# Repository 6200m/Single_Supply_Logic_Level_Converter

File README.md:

SparkFun Single Supply Logic Level Converter
========================================

[*SparkFun Single Supply Logic Level Converter (PRT-14765)*](https://www.sparkfun.com/products/14765)

The SparkFun Single Supply Logic Level Converter is logic level and power supply translator in one small package. This little board breaks out the Texas Instruments TXB0104 4-bit bi-directional voltage-level translator with automatic direction sensing. With this logic level converter you will be able to use your 5V logic microcontroller with 3.3V sensors without the second power supply!

What makes this logic level converter truly special is the fact that you can supply it with 3.3V and it will create the 5V - meaning you can use your 3.3V system, and convert directly to another 5V sensor - and even power your sensor or other board!

This logic level converter provides 5V to the high side of the TXB0104 and the low side is programmable to 3.3V, 2.5V and 1.8V. Please keep in mind that the default low side voltage is 3.3V.

Repository Contents
-------------------
* **/Firmware** - Example code 
* **/Hardware** - Eagle design files (.brd, .sch)
* **/Production** - Production panel files (.brd)

Documentation
--------------
* **[Hookup Guide](https://learn.sparkfun.com/tutorials/single-supply-logic-level-converter-hook-up-guide)** - Basic hookup guide for the Single Supply Logic Level Converter.
* **[SparkFun Fritzing repo](https://github.com/sparkfun/Fritzing_Parts)** - Fritzing diagrams for SparkFun products.

Product Versions
----------------
* [PRT-14765](https://www.sparkfun.com/products/14765)- V1.0

License Information
-------------------

This product is _**open source**_! 

Please review the LICENSE.md file for license information. 

If you have any questions or concerns on licensing, please contact techsupport@sparkfun.com.

Distributed as-is; no warranty is given.

- Your friends at SparkFun.

_<COLLABORATION CREDIT>_

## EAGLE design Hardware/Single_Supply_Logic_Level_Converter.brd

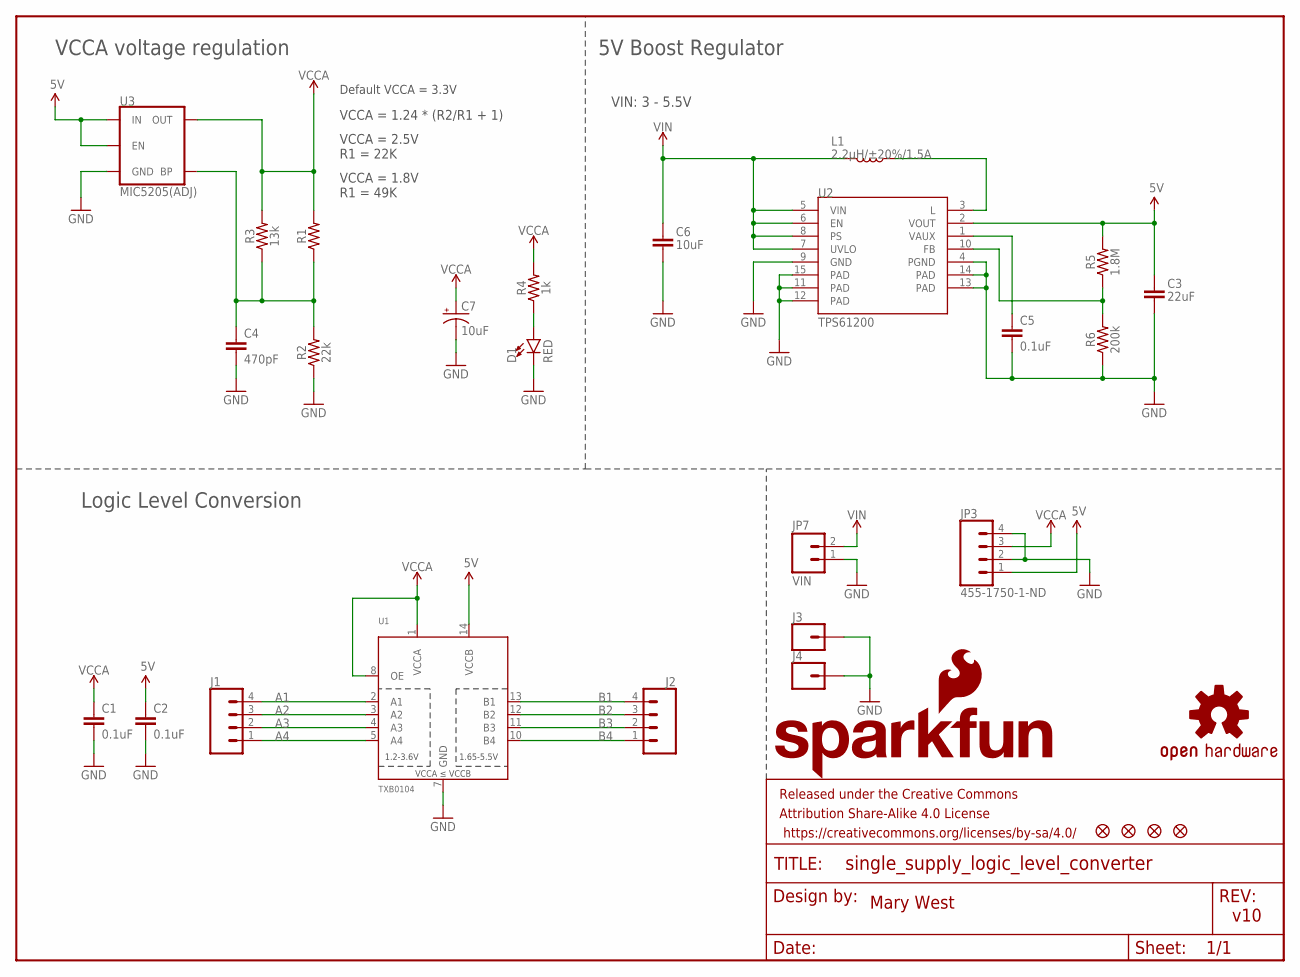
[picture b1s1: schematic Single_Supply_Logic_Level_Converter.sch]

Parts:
C1, C2: 0.1uF; 0603-CAP
C3: 22uF; 0805
C4: 470pF; 0603
C5: 0.1uF; 0603
C6: 10uF; 0603
C7: 10uF; EIA3216
D1: RED; LED-0603
FD1, FD2, FD3, FD4: FIDUCIALUFIDUCIAL; FIDUCIAL-MICRO
FRAME1: FRAME-LETTER; CREATIVE_COMMONS
J1, J2: CONN_04; 1X04
J3, J4: CONN_01; 1X01
JP3: 455-1750-1-ND; 1X04
JP7: VIN; 1X02
L1: 2.2µH/±20%/1.5A; INDUCTOR_2.2UH
LOGO1: SFE_LOGO_NAME_FLAME.1_INCH; SFE_LOGO_NAME_FLAME_.1
LOGO2: OSHW-LOGOS; OSHW-LOGO-S
R1: AXIAL-0.3
R2: 22k; 0603
R3: 13k; 0603
R4: 1k; 0603
R5: 1.8M; 0603
R6: 200k; 0603
U1: TXB0104; TSSOP14
U2: TPS61200; QFN-10_PAD
U3: MIC5205(ADJ); SOT23-5

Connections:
5V: C2.1, C3.1, JP3.1, R5.2, U1.14 (VCCB), U2.2 (VOUT), U3.1 (IN), U3.3 (EN)
A1: J1.4, U1.2 (A1)
A2: J1.3, U1.3 (A2)
A3: J1.2, U1.4 (A3)
A4: J1.1, U1.5 (A4)
B1: J2.4, U1.13 (B1)
B2: J2.3, U1.12 (B2)
B3: J2.2, U1.11 (B3)
B4: J2.1, U1.10 (B4)
FB: R5.1, R6.2, U2.10 (FB)
GND: C1.2, C2.2, C3.2, C4.2, C5.2, C6.2, C7.-, D1.C, J3.1, J4.1, JP3.2, JP3.4, JP7.1, R2.1, R6.1, U1.7 (GND), U2.4 (PGND), U2.9 (GND), U2.11 (PAD), U2.12 (PAD), U2.13 (PAD), U2.14 (PAD), U2.15 (PAD), U3.2 (GND)
unnamed: D1.A, R4.1
unnamed: L1.P$1 (1), U2.3 (L)
unnamed: C5.1, U2.1 (VAUX)
unnamed: C4.1, R1.P$1 (1), R2.2, R3.1, U3.4 (BP)
VCCA: C1.1, C7.+, JP3.3, R1.P$2 (2), R3.2, R4.2, U1.1 (VCCA), U1.8 (OE), U3.5 (OUT)
VIN: C6.1, JP7.2, L1.P$2 (2), U2.5 (VIN), U2.6 (EN), U2.7 (UVLO), U2.8 (PS)

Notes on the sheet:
Mary West
v10
VIN: 3 - 5.5V
Default VCCA = 3.3V
Logic Level Conversion
VCCA voltage regulation
5V Boost Regulator
VCCA = 1.24 * (R2/R1 + 1)
VCCA = 2.5V R1 = 22K
VCCA = 1.8V R1 = 49K

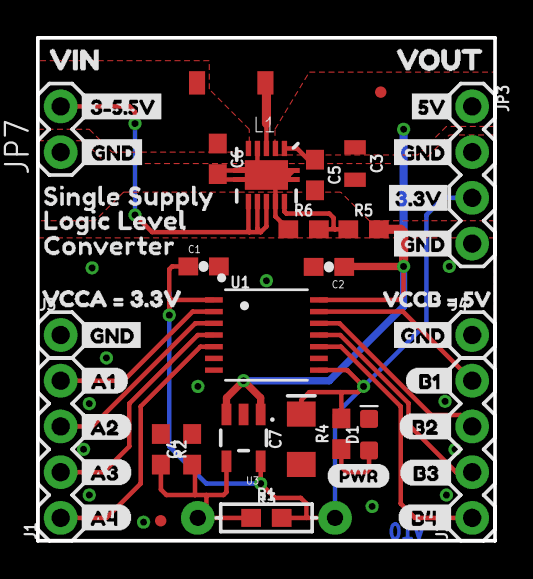
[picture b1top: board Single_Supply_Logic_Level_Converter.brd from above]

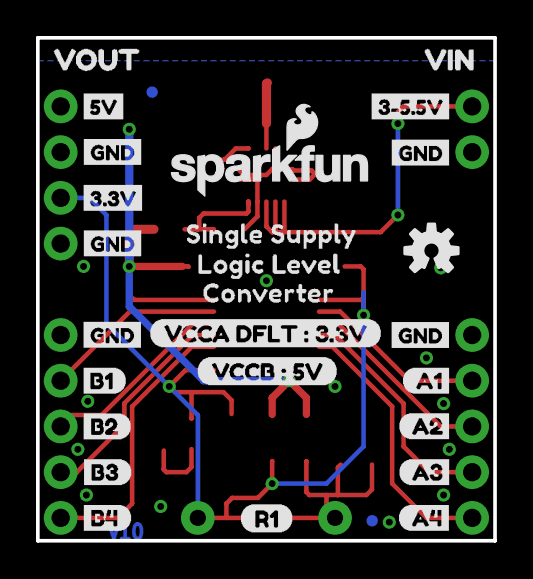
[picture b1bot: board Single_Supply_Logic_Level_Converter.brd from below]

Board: 2 copper layers, 25.4 x 27.9 mm, 79 parts (28 on the bottom side), 17 nets.

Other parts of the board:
U$7, U$24, U$31, U$34, U$35, U$40, U$41, U$52, U$54, U$55: GND0
U$8, U$38: VIN1
U$9: A10
U$10, U$43: CONVERTER0
U$11, U$45: LOGIC_LEVEL2
U$12, U$46: SINGLE_SUPPLY1
U$13: B1_12
U$14: A21
U$15: A32
U$16: A43
U$17: B14
U$18: B25
U$19: B2_11
U$20: B3_10
U$21, U$39: 3#5#5V3
U$22: B4_9
U$23, U$53: 3#3V2
U$25: A14
U$26: A28
U$27, U$44: VOUT2
U$28: A35
U$29: PWR0
U$30: A46
U$32, U$51: 5V1
U$33: B36
U$36: VCCA_#_3#3V0
U$42: B47
U$47: VCCA_DFLT_#_3#3V0
U$48: VCCB_#_5V0
U$49: R10
U$56: VCCB_#_5V1

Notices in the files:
parts and their libraries:
SparkFun-Capacitors: Licensing: CC v3.0 Share-Alike You are welcome to use this library for commercial purposes.
SparkFun-Aesthetics: Released under the Creative Commons Attribution Share-Alike 4.0 License
SparkFun-Aesthetics: https://creativecommons.org/licenses/by-sa/4.0
